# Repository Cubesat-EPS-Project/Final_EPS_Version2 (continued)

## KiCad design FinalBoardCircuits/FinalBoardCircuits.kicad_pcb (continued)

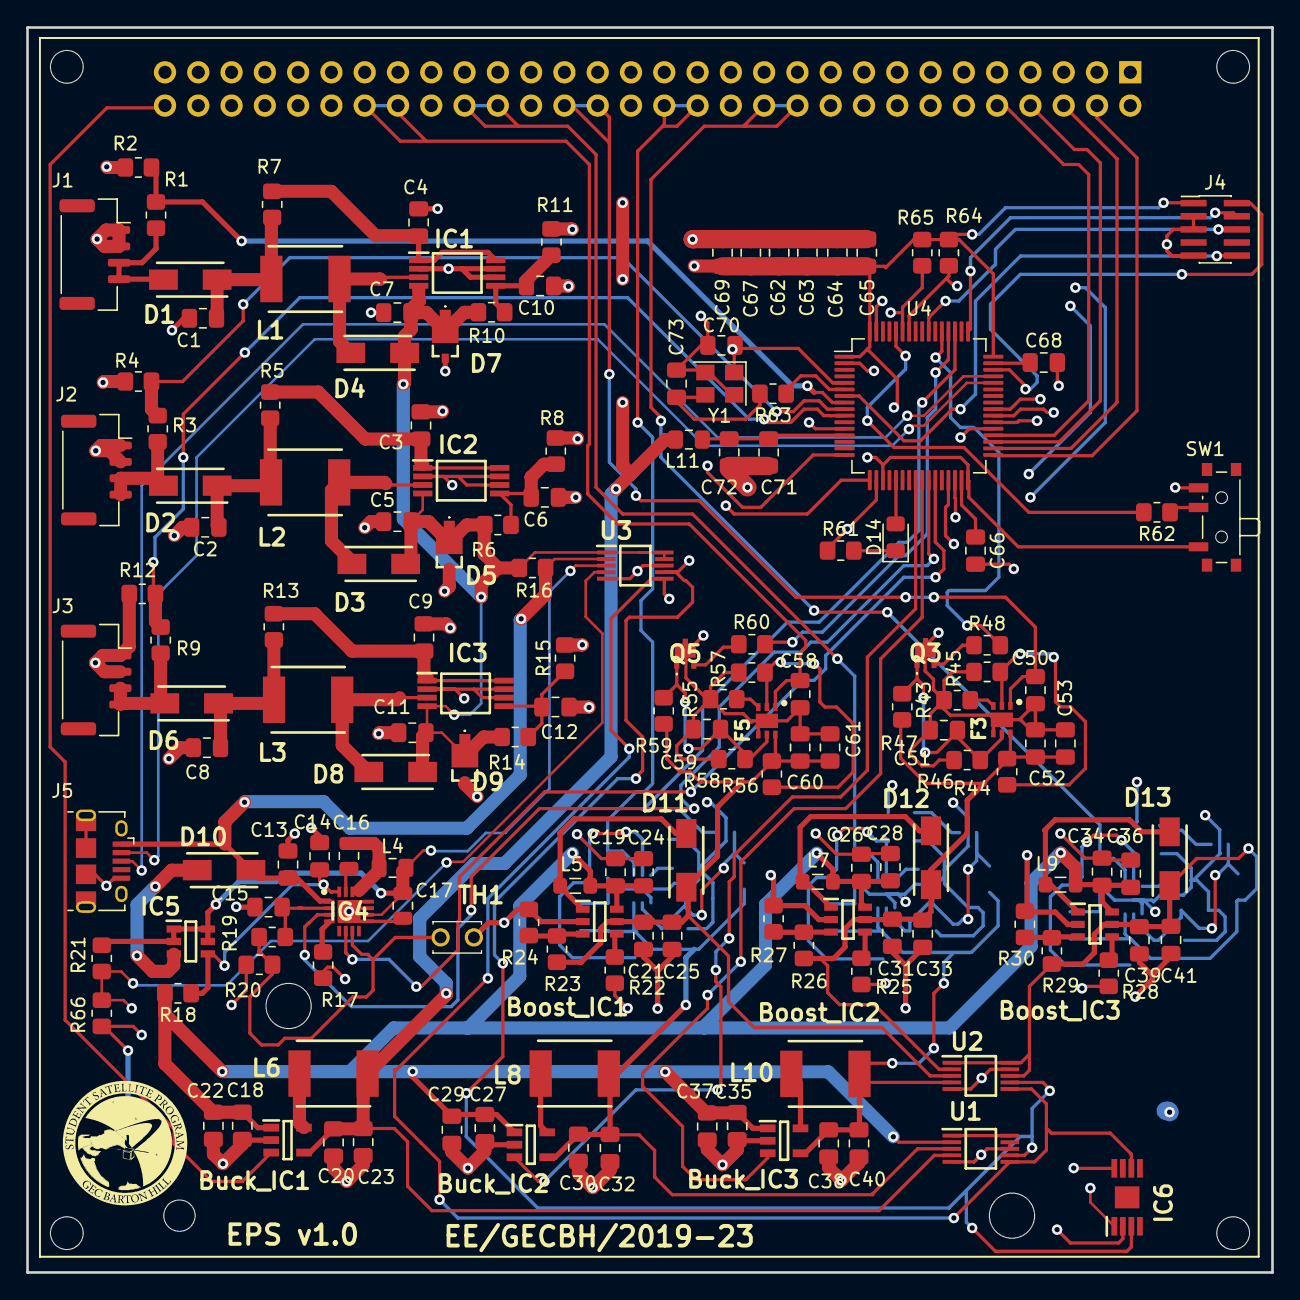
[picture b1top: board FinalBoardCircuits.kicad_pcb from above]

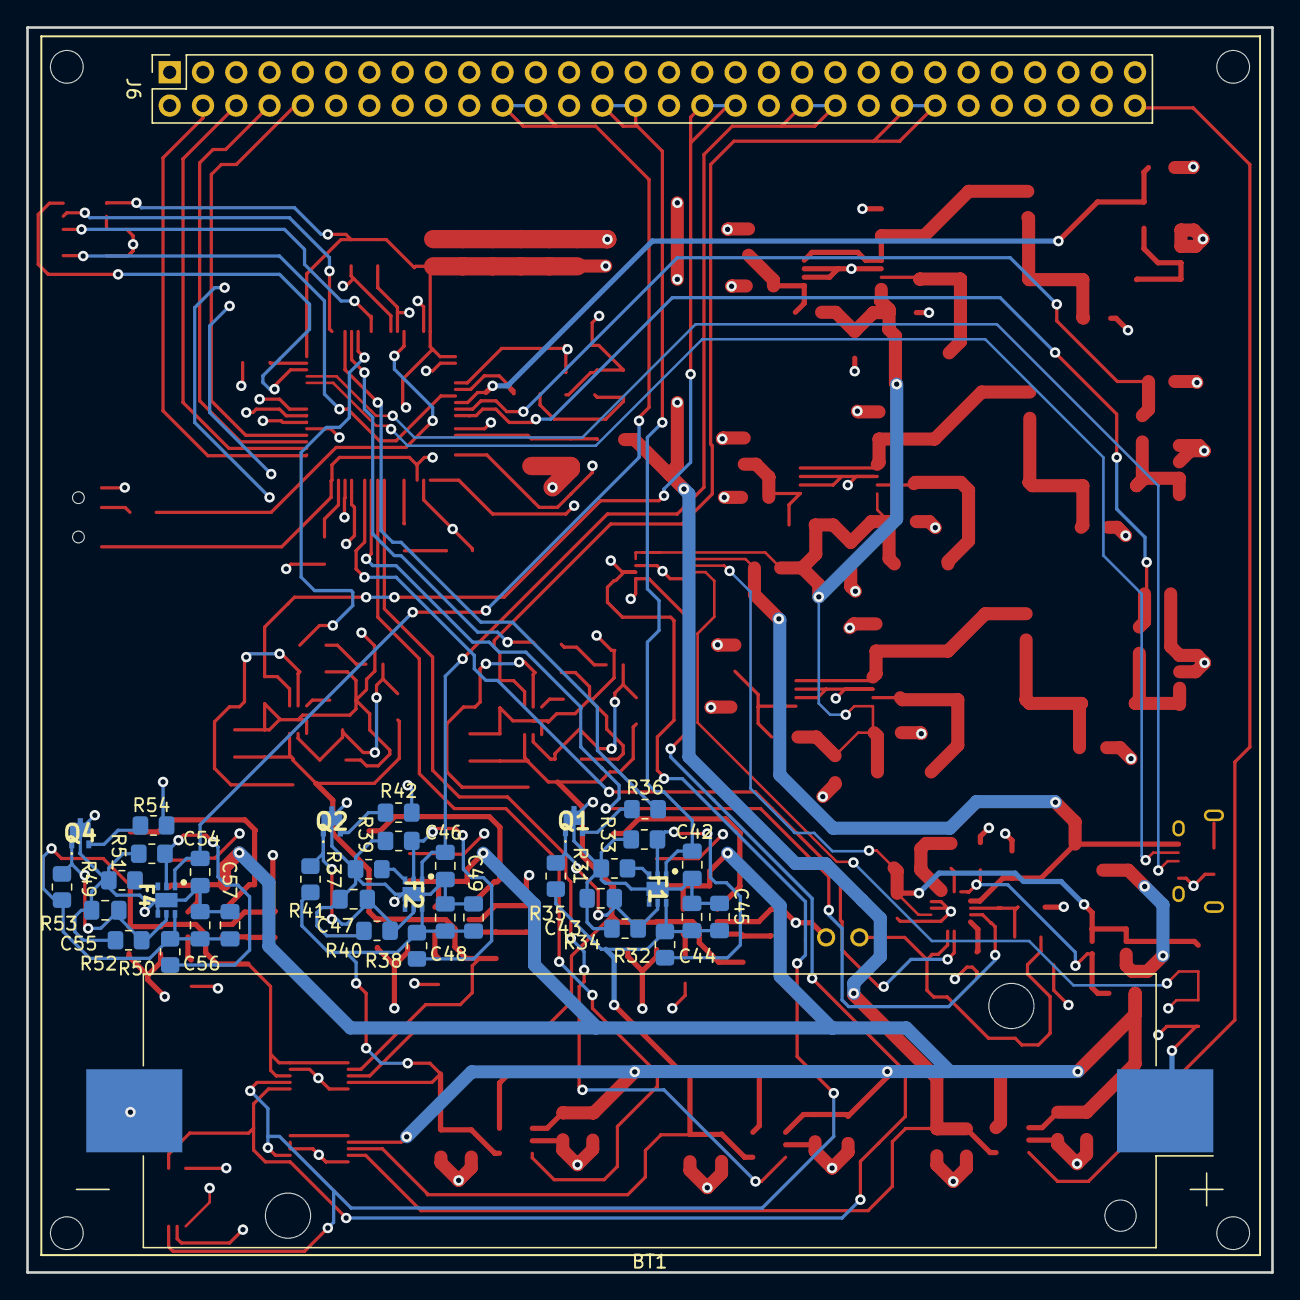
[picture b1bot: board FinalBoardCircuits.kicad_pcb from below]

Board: 4 copper layers, 95.0 x 95.0 mm, 200 parts (38 on the bottom side), 115 nets.

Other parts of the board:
IC6: LTC2941IMS8E#PBF; SOP65P490X110-9N
R66: 0.025; R_0805_2012Metric_Pad1.20x1.40mm_HandSolder

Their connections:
I2C1_SCL: IC6.3 (SCL); also elsewhere on the board
I2C1_SDA: IC6.6 (SDA); also elsewhere on the board

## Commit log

2023-06-01 Final board 2nd version
    Final EPS board with 3 mppt, 1 battery charger, 3 5V regulator, 3 3.3V regulator, 6 overvoltage and overcurrent protection, and an stm32 chip in a PC104 architecture
2023-06-03 Added fuel guage
    Added fuel guage circuit to the final design.
